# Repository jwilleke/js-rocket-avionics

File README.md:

# js-rocket-avionics

Carrier PCB and flight firmware for the [js-rocket](https://github.com/jwilleke/js-rocket) electronics sled.

__This is one candidate payload for the rocket, not *the* payload.__ The rocket flies on ballast alone. The interface it has to satisfy — 40.0 mm bore × 150 mm, an M3 × 55 retainer at nose z 15, a ~50 g mass ceiling, an optional camera port — is [`js-rocket/docs/payload-bay.md`](https://github.com/jwilleke/js-rocket/blob/main/docs/payload-bay.md), and that is the only page in that repo this project depends on.

__Flying the rocket, not building it? Read [docs/using-avionics.md](docs/using-avionics.md)__ — what the electronics do, and what to do before, during and after a flight. Everything below is for builders.

Separate from the rocket repo on purpose: `js-rocket` is geometry and documentation with no code, no package manager and no dependencies, and its `CLAUDE.md` says so explicitly. Copper, firmware and __the design record — every decision and why, in [docs/design.md](docs/design.md)__ — live here instead.

__Why it is built this way is in [docs/design.md](docs/design.md).__ __Every part this project needs is in [docs/BOM.md](docs/BOM.md), which is the single source of truth for part numbers and weights__ — plus what each part is, which board it serves, and what was rejected. __What to change next time, and what can be bought ready-made, is in [docs/next-electronics.md](docs/next-electronics.md).__ __What was actually bought is in [docs/shopping-list.md](docs/shopping-list.md)__ — orders, costs, arrival status. The printed sled that carries these boards, and the [PayloadAdapter](https://github.com/jwilleke/js-rocket/blob/main/docs/3d-printed-parts/payload-adapter.md) it loads through, are rocket parts and stay in [js-rocket](https://github.com/jwilleke/js-rocket).

__Status: one two-sided board ([PCB-carrier-design.md](hardware/PCB-carrier/PCB-carrier-design.md)), placed, netted and routed. DRC: 0 violations, 0 unconnected.__ The generator routes the signal nets itself ([`carrier_router.py`](hardware/scripts/carrier_router.py), [#15](https://github.com/jwilleke/js-rocket-avionics/issues/15)); ground and 3.3 V reach every pad through the two inner planes. What the board is, both sides with a drawing, is [hardware/PCB-carrier/PCB-carrier.md](hardware/PCB-carrier/PCB-carrier.md).

> __Do not order it yet.__ Left before ordering: the reprinted fit mock, fitted, and the pre-order review — regenerate the fabrication files from this board and read its connections back ([#16](https://github.com/jwilleke/js-rocket-avionics/issues/16)).

## What a flight records

__Planned, not yet written.__ The recorder firmware on XIAO-ESP32S3-cam is __not started__ — today a flight would record nothing. The GPS is not recorded at all; its only copy is what the ground receiver hears.

| Data | From | Recorded? | Where it ends up |
|---|---|---|---|
| Acceleration and rotation | [LSM6DSO32](hardware/LSM6DSO32/LSM6DSO32.md), XIAO-ESP32S3-cam | __planned__ — 500 Hz, read from the sensor's FIFO | PSRAM through the flight (~900 KB a minute), __written to microSD in slices as it goes__ |
| Pressure, so altitude | [BMP388](hardware/BMP388-barometer/BMP388-barometer.md), XIAO-ESP32S3-cam | __planned__ — in the same log | the same |
| Video | OV3660 on the [Sense camera board](hardware/Sense-camera-board/Sense-camera-board.md), XIAO-ESP32S3-cam | __planned__ — from launch, with a few seconds before it, until landing is detected; idle on the pad | microSD, as it records |
| Position and GPS altitude | [L76K-GNSS](hardware/L76K-GNSS/L76K-GNSS.md), XIAO-ESP32S3-lora | __no__ — broadcast over LoRa by stock Meshtastic every so often, stored nowhere on the rocket | the ground receiver and the phone on it — [#23](https://github.com/jwilleke/js-rocket-avionics/issues/23), ordered 2026-09-11 |

__Two things that follow:__

- __A reset of XIAO-ESP32S3-cam in flight loses the slice of the sensor log not yet on the card__ — the rest is already written. Whether the shared battery browns it out is [#8](https://github.com/jwilleke/js-rocket-avionics/issues/8)
- __The sensor log has no GPS in it.__ The two XIAOs share power and nothing else, so position and motion are never in one record

Why the log sits in PSRAM rather than going straight to the card: [design.md](docs/design.md#data-path--why-the-log-lives-in-psram).

## The interface to the sled

__One board on the PayloadSled's centre line__, hanging off the web on two standoffs: the tall side (both XIAO stacks) faces 270°, the camera port; the low side (sensors, standoffs) faces 90°, the web. The sled side is [js-rocket#99](https://github.com/jwilleke/js-rocket/issues/99), which moves the web toward 90° and drills it at the standoffs. __Change these and the sled changes.__

| | Value |
|---|---|
| Board | __24.0 × 115.7 mm__, aft end at nose z 25.4, forward end 141.1 |
| Thickness | __1.6 mm__, 4 copper layers — OSH Park's only 4-layer thickness |
| Corner radius | 2.0 mm |
| Standoffs | __2 plain M3 holes__ (3.2 mm) at board (x, y) __(12.0, 4.0)__ and __(16.5, 110.5)__ — nose z 29.4 and 135.9, neither under a module. A __female-female M3 hex standoff__, 10 mm, between the board's low face and the web, a screw into it from each side, as on the fit mock — nothing soldered |
| XIAO-ESP32S3-cam centre | board y __18.0__ (nose z 43.4), under the camera pad |
| XIAO-ESP32S3-lora centre | board y __41.4__ (nose z 66.8), turned 90° |

Board x runs across the board, y from the aft end, forward positive, in KiCad's top view (the tall side). Everything above is read out of the generated board by `gen_carrier.py`; the gerbers in `fab/` predate it ([#16](https://github.com/jwilleke/js-rocket-avionics/issues/16)).

__Why 24 mm wide.__ It matches the web. The sensors fit across it or hang just past its edges, below the web — [PCB-carrier.md](hardware/PCB-carrier/PCB-carrier.md#low-side--faces-90-the-web).

__Why 115.7 mm long.__ The camera fixes the cam XIAO at the aft end, and the tall side then carries the lora XIAO, the L76K-GNSS, the data-link jumpers and the buzzer end to end. The low side carries the battery as well as the sensors (layout B2, 2026-09-15): LSM6DSO32 aft, the battery behind the lora XIAO and the L76K, the BMP388 forward of it, turned across the board under the buzzer ([#36](https://github.com/jwilleke/js-rocket-avionics/issues/36)). 90.4 mm until the battery moved onto the board.

__Why 1.6 mm.__ It is the only thickness OSH Park makes a 4-layer board in — "63mil (1.6mm) nominal". The 1.0 mm this page carried until 2026-09-15 was never checked against the fab; the operator caught it on the printed fit mock ("looks too thin"). It is also the better board: the standoffs are now __106.5 mm apart__ (81 before 2026-09-15), and 1.6 mm is __about 4× as stiff__ as 1.0 over that span (stiffness goes as thickness cubed). The low face — the standoffs' face — stays at r 0.5, so the sled does not change; the tall side moves __0.6 mm toward 270°__. What that costs across the bore is in [PCB-carrier-design.md](hardware/PCB-carrier/PCB-carrier-design.md#across-the-bore)

## The XIAO stack

__The expansion board — Sense or Wio-SX1262 — sits above the XIAO__, on the B2B connector on its front face. The XIAO stands on __two standard 7-pin headers__, ~2.50 mm, onto the board. No cutout and no tall stacking headers are needed. Stack heights and the fit across the bore are in [docs/design.md](docs/design.md#headers-and-the-expansion-board-on-top).

## Connections

There is __no schematic file__. Nets are assigned to pads directly in the generator, which is more robust than hand-authoring schematic s-expressions for 11 nets and keeps one generator as the single source of truth. The cost is no ERC and no drawn diagram — so this table *is* the wiring diagram. __Keep it in step with `gen_carrier.py`.__

| Net | From | Also reaches |
|---|---|---|
| `GND` | both XIAOs, pin 13 | In1 plane, every module |
| `+3V3` | XIAO-ESP32S3-cam pin 12 __only__ | In2 plane; LSM6DSO32 `VIN`; BMP388 `VIN` __and `CS`__ (I2C mode, [#19](https://github.com/jwilleke/js-rocket-avionics/issues/19)) |
| `+3V3_LORA` | XIAO-ESP32S3-lora pin 12 | the L76K-GNSS's `3V3` only — __kept off the plane__, so the two regulators are never paralleled |
| `SDA` | cam __D4__ (pin 5, GPIO5) | LSM6DSO32, BMP388 |
| `SCL` | cam __D5__ (pin 6, GPIO6) | LSM6DSO32, BMP388 |
| `BUZZER` | cam __D0__ (pin 1, GPIO1) | one buzzer lead (`TP_BUZ`); the PS1240 sits on the tall side's forward end |
| `BUZZER_B` | cam __D2__ (GPIO3) | the other buzzer lead (`TP_BUZ_G`), driven in opposite phase to `BUZZER` for about +6 dB ([#25](https://github.com/jwilleke/js-rocket-avionics/issues/25)) |
| `GPS_TX` | lora __D6__ (pin 7, GPIO43) | the L76K-GNSS's pad at the D6 position, which is the module's __RX__ |
| `GPS_RX` | lora __D7__ (pin 8, GPIO44) | the L76K-GNSS's pad at the D7 position, which is the module's __TX__ |
| `LINK_GPS` | the GPS link's 2-pin header, pin 2 (pin 1 is on `GPS_RX`) | its 1 kΩ, whose far end is `GPS_CAM` |
| `LINK_EVT` | the event link's 2-pin header, pin 1 | its 1 kΩ, whose far end is `EVT_CAM` |
| `GPS_CAM` | XIAO-ESP32S3-cam __D1__ (GPIO2) | the GPS link's 1 kΩ: the cam XIAO hears the GPS ([#26](https://github.com/jwilleke/js-rocket-avionics/issues/26)) |
| `EVT_CAM` | XIAO-ESP32S3-cam __D3__ (GPIO4) | the event link's 1 kΩ: event text out |
| `EVT_LORA` | XIAO-ESP32S3-lora __D1__ (GPIO2) | the event link's 2-pin header, pin 2: Meshtastic's Serial module receives here. Stock Meshtastic leaves D1 free ([#26](https://github.com/jwilleke/js-rocket-avionics/issues/26)) |

`GPS_TX` and `GPS_RX` are named from the XIAO's side. __Wire the L76K-GNSS by position, never by its silkscreen word__ — [L76K-GNSS.md](hardware/L76K-GNSS/L76K-GNSS.md#pinout--from-seeeds-schematic-not-the-listing).

### The pin map, and an error worth not repeating

The KiCad footprint numbers its pads 1–14 with no signal names, DIP-style — 1 at top-left, down to 7 at bottom-left, 8 at bottom-right, up to 14 at top-right. Seeed's pinout gives the meaning:

```text
pin  1  2  3  4  5  6  7   8  9  10  11   12   13   14
sig  D0 D1 D2 D3 D4 D5 D6  D7 D8 D9  D10  3V3  GND  5V
```

An earlier revision of the generator put GPS on pins 6/7 and I2C on 4/5 — which are __D5/D6 and D3/D4, every one off by one__. Caught by reading the mapping back out of the saved board rather than trusting the script's own output. The generator now names pins (`XIAO_PIN["D6"]`) so the numbers never appear by hand.

__Each 1×7 header numbers its own pads 1–7.__ The second row's pad 1 is XIAO pin 8, at the far end, so `xiao_pin = pad + 7` running back toward the USB-C. This file once said `15 − pad`, which is [#18](https://github.com/jwilleke/js-rocket-avionics/issues/18)'s mirrored row, written down as the rule.

## The GPS is an L76K

The MAX-M10S was rejected on 2026-08-06: __44.2 × 30.5 mm — wider than this 24 mm board — and ~$60__. The chosen part is Seeed's __L76K GNSS for XIAO (109100021)__ — 18 × 21 mm, UART on __D6/D7__. It takes its own footprint on the tall side, forward of the lora XIAO ([where](hardware/PCB-carrier/PCB-carrier.md#tall-side--faces-270-the-camera)), and its antenna is a separate part on the sled. Pinout, power and orientation: [L76K-GNSS.md](hardware/L76K-GNSS/L76K-GNSS.md).

The same staleness once reached the barometer: __BMP390 → BMP388__, settled on 2026-08-06 when the 390 went out of stock. Same BMP3xx driver, same 25.5 × 17.8 mm STEMMA QT outline, address 0x77, and its pinout __confirmed off the physical part__.

## Battery — read before assembling

__BAT+/BAT− are underside pads on the XIAO__, not brought out to the castellated edge, so the battery cannot reach a XIAO through the headers. The battery reaches each XIAO through a __Y-cable__, off the board, and a short __soldered pigtail__ on its BAT pads.

- __Solder the pigtails before the XIAO goes onto its headers.__ The board, not the expansion board, is what covers the pads.
- __On battery power there is no voltage on the 5V pin__ — nothing can be fed from a XIAO's 5V rail.
- Both XIAO chargers sit in parallel on one battery. __Charge through one USB port at a time__, and read [why that is not sufficient on its own](hardware/LiPo-500mAh/LiPo-500mAh.md#two-chargers-on-one-battery).
- __The battery is not on the board.__ A Y-cable joins it to both XIAOs' pigtails ([LiPo-500mAh.md](hardware/LiPo-500mAh/LiPo-500mAh.md#the-y-cable)). Check every new cable's polarity with a meter; reversing a LiPo into a XIAO destroys it.

## No RF on this board

The L76K and the Wio-SX1262 each carry their own U.FL connector, and both antennas mount on the sled, so __no RF ever crosses the carrier__. It is a purely digital and power board of 9 nets, which is what makes it tractable to generate and verify headlessly.

## Building

Requires KiCad 10. The generator uses KiCad's bundled Python so `pcbnew` matches the CLI exactly.

```bash
KPY=/Applications/KiCad/KiCad.app/Contents/Frameworks/Python.framework/Versions/3.9/bin/python3
CLI=/Applications/KiCad/KiCad.app/Contents/MacOS/kicad-cli

$KPY hardware/scripts/gen_carrier.py
$CLI pcb drc  --format json -o /tmp/drc.json hardware/PCB-carrier/PCB-carrier.kicad_pcb
$CLI pcb export gerbers -o fab/gerbers/ hardware/PCB-carrier/PCB-carrier.kicad_pcb
$CLI pcb export drill   -o fab/gerbers/ hardware/PCB-carrier/PCB-carrier.kicad_pcb
```

__The board is generated, not hand-edited.__ `.kicad_pcb` format shifts between KiCad releases; building it through `pcbnew` means the file is written by the same code that reads it. Edit `hardware/scripts/gen_carrier.py` and re-run — do not edit the board file directly, or the next run overwrites you.

`gen_outline.py` is the superseded 2a-only version, kept for reference.

DRC must report __0 violations__ before anything is ordered.

## Remaining stages

| Stage | State |
|---|---|
| 2a — outline, standoffs, stackup | __done__, one two-sided board |
| 2b — nets + footprints | __done__ — every footprint placed and netted |
| 2b — GND/+3V3 planes | __done__, In1 and In2 filled |
| 2c — placement | __done in the generator__, pending review of the drawing — [#14](https://github.com/jwilleke/js-rocket-avionics/issues/14) |
| 2d — signal routing | not started — [#15](https://github.com/jwilleke/js-rocket-avionics/issues/15) |
| 2e — Gerber + drill for fab | chain proven; needs a finished board |

__Do not order copper before breadboarding.__ A layout error costs ~$43 and two weeks; a wiring error costs minutes.

Fab target is __OSH Park__. The 24 × 70 mm version quoted **$26.00 for 3 copies** — OSH Park's 4-layer price is $10/in² for three — so 24 × 115.7 mm (4.30 in²) should land near __$43__. Re-upload to confirm; three copies — one to fly, two spares.

__OSH Park accepts the `.kicad_pcb` directly__ — confirmed by upload, not assumed. It read the layer count and outline unaided, so `fab/gerbers/` is not in the ordering path and exists only as a check that the export chain works.

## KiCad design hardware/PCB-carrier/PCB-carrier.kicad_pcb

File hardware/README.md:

# Hardware

__One page per part, and the source of truth for the hardware in use.__ What each part is, its interfaces and dimensions, and the traps that are properties of the object.

__These pages are not a history and not a task list.__ They say what is, not what changed or what to do next. Decisions and open work live in [issues](https://github.com/jwilleke/js-rocket-avionics/issues); what happened in a session lives in `private/project_log.md`; the reasoning behind the design lives in [design.md](../docs/design.md).

__These pages also fix the vocabulary.__ A part is called by the name of its page here — [XIAO-ESP32S3-cam](XIAO-ESP32S3-cam/XIAO-ESP32S3-cam.md) and [XIAO-ESP32S3-lora](XIAO-ESP32S3-lora/XIAO-ESP32S3-lora.md), never "board A" and "board B" — and where a page has a plain-English word for the thing, that word is the one to use. __The [LiPo-500mAh](LiPo-500mAh/LiPo-500mAh.md) is the battery.__ It is not "the cell": that is a word from datasheets, it reads as jargon to everyone who has to work on this, and one battery made of one cell gains nothing by the distinction.

## The names, and where they live

__One folder per part. The folder, the page inside it and the part all carry the same name.__ Adopted 2026-09-09. `hardware/BMP388-barometer/BMP388-barometer.md` — not `README.md`, because a folder that already names the part does not need a second word for it. __A part's own photographs live in its folder__, beside its page.

__These are the names. Nothing else is a name for these things:__

| Folder and page | Is |
|---|---|
| `XIAO-ESP32S3-cam` | The MCU module carrying the camera. Never "board B", never "the Sense one" |
| `XIAO-ESP32S3-lora` | The MCU module carrying the radio. Never "board A" |
| `Sense-camera-board` | The expansion board on XIAO-ESP32S3-cam |
| `Wio-SX1262-LoRa` | The LoRa radio |
| `L76K-GNSS` | The GNSS module |
| `LSM6DSO32` | The IMU |
| `BMP388-barometer` | The barometer |
| `PS1240-buzzer` | The buzzer |
| `LiPo-500mAh` | __The battery.__ Never "the cell" |
| `Arming-switch` | The arming switch. __Not the JST__, which is a connector |
| `Stacking-headers` | The 7-pin strips |
| `Antennas` | Both U.FL antennas |
| `microSD` | The card |
| `PCB-carrier` | The carrier board |
| `LiPo-charger` | The battery's own USB charger, off the rocket. Not "the charger" alone — each XIAO has one built in too |
| `camera-stack` | XIAO-ESP32S3-cam __with__ its Sense board — the assembly, not either part |
| `GNSS-stack` | __A rejected arrangement, not a thing that exists.__ Kept so it is not proposed again |

__Where a part has no folder here, it is not a part of this payload.__ "XIAO" on its own is not a name: there are two of them and they are not interchangeable.

__Two exceptions to "photographs live with the part".__ [`docs/resources/`](../docs/resources/) keeps the images that belong to __both__ XIAO modules — the front and back pinouts, the module and underside shots — because they document the model rather than either role, and a second copy is a copy that drifts. [`docs/bench-work/`](../docs/bench-work/) keeps what belongs to no part at all: the breadboard drawing, the bench photograph and the measurement grid.

__These pages hold no part numbers and no masses.__ [BOM.md](../docs/BOM.md) owns both and says so: *"anything else that quotes a part number or a mass is wrong — link here instead."* A number in two places is a number that will disagree with itself.

| | Page | Goes with | Photos | What it is |
|---|---|---|---|---|
| MCU | [XIAO-ESP32S3-lora.md](XIAO-ESP32S3-lora/XIAO-ESP32S3-lora.md) | — | grid | The MCU module. __Runs stock Meshtastic__ — identical to the cam copy to look at; [which is which](XIAO-ESP32S3-lora/XIAO-ESP32S3-lora.md#which-xiao-is-this-one) |
| MCU | [XIAO-ESP32S3-cam.md](XIAO-ESP32S3-cam/XIAO-ESP32S3-cam.md) | — | grid + bench | The MCU module. On the bench with both sensors and the buzzer; runs `bringup-cam` |
| Payload | [Sense-camera-board.md](Sense-camera-board/Sense-camera-board.md) | XIAO-ESP32S3-cam | grid ×2 | OV3660 camera and the microSD slot |
| Radio | [Wio-SX1262-LoRa.md](Wio-SX1262-LoRa/Wio-SX1262-LoRa.md) | XIAO-ESP32S3-lora | grid | LoRa. Buy as the matched kit, never separately |
| GNSS | [L76K-GNSS.md](L76K-GNSS/L76K-GNSS.md) | XIAO-ESP32S3-lora | grid | Position. __Flat on the carrier's tall side__, own footprint |
| Sensor | [LSM6DSO32.md](LSM6DSO32/LSM6DSO32.md) | carrier | grid + back | ±32 g IMU with a 9 KB FIFO |
| Sensor | [BMP388-barometer.md](BMP388-barometer/BMP388-barometer.md) | carrier | grid + 2 close | Unported barometer, 0x77 |
| Output | [PS1240-buzzer.md](PS1240-buzzer/PS1240-buzzer.md) | carrier | __none__ | Passive piezo. The only status channel on the pad |
| Power | [LiPo-500mAh.md](LiPo-500mAh/LiPo-500mAh.md) | carrier | __none__ | One battery, both XIAOs |
| Power | [LiPo-charger.md](LiPo-charger/LiPo-charger.md) | off the rocket | __none__ | Charges the battery at its own plug, below the sled |
| Power | [Arming-switch.md](Arming-switch/Arming-switch.md) | battery lead | __n/a__ | In the battery line. __Flight 3 carries none__ |
| Storage | [microSD.md](microSD/microSD.md) | Sense camera board | __none__ | Video only |
| RF | [Antennas.md](Antennas/Antennas.md) | Wio-SX1262, L76K | grid | Both off-board on U.FL. ≥50 mm apart |
| Mechanical | [Stacking-headers.md](Stacking-headers/Stacking-headers.md) | both XIAOs | __none__ | 7-pin strips, ~2.50 mm standoff |
| Mechanical | [PCB-carrier.md](PCB-carrier/PCB-carrier.md) | everything | __n/a__ | The board, and the sled's structural span |
| Assembly | [camera-stack.md](camera-stack/camera-stack.md) | — | end + side | XIAO-ESP32S3-cam with its Sense board, as one object |
| Assembly | [GNSS-stack.md](GNSS-stack/GNSS-stack.md) | — | __none__ | __Rejected.__ Why the L76K is not in a stack |

## Photographs

__Each part's images live in that part's folder__, beside its page; the two shared XIAO images stay in [`docs/resources/`](../docs/resources/). Every one is embedded on the page above. __Shot on the printed measurement grid__ — part flat, square-on, calibration bar in frame. Method and its precision: [module-pinouts.md](../docs/module-pinouts.md#how-these-are-measured--photograph-on-the-grid-not-calipers).

| Image | Part | What it is for |
|---|---|---|
| [`BMP388-front-grid.jpg`](BMP388-barometer/BMP388-front-grid.jpg) | BMP388 | __Dimensional record.__ Header row along the bottom, mounting holes at the top corners |
| [`BMP388-front.jpg`](BMP388-barometer/BMP388-front.jpg) | BMP388 | Close-up. Confirms pin order on the silkscreen |
| [`BMP388-back.jpg`](BMP388-barometer/BMP388-back.jpg) | BMP388 | Close-up. Address jumper, `3 V` marking |
| [`LSM6DSO32-front.jpg`](LSM6DSO32/LSM6DSO32-front.jpg) | LSM6DSO32 | __Dimensional record.__ Both header rows and both mounting holes |
| [`LSM6DSO32-back.jpg`](LSM6DSO32/LSM6DSO32-back.jpg) | LSM6DSO32 | Close-up. `ST LSM6DSO32`, ±32 g, `0x6A` |
| [`L76K-GNSS.jpg`](L76K-GNSS/L76K-GNSS.jpg) | L76K | Module and its ≈25 mm patch antenna, to scale |
| [`Wio-SX1262-LoRa.jpg`](Wio-SX1262-LoRa/Wio-SX1262-LoRa.jpg) | Wio-SX1262 | FCC ID, U.FL, and the 2×5 header currently fitted |
| [`Wio-SX1262-LoRa-antennas.jpg`](Wio-SX1262-LoRa/Wio-SX1262-LoRa-antennas.jpg) | Antennas | Both Seeed strips, to scale |
| [`XIAO-ESP32S3-module.jpg`](../docs/resources/XIAO-ESP32S3-module.jpg) | XIAO ×2 | The MCU board. USB-C, U.FL, B2B, 14 pads |
| [`XIAO-ESP32-S3-bottom.jpg`](../docs/resources/XIAO-ESP32-S3-bottom.jpg) | XIAO ×2 | __The pin labels.__ Underside, where the silkscreen is — the only reading that confirms pad 1 is `D0`. See [module-pinouts.md](../docs/module-pinouts.md#xiao-esp32s3--read-off-the-underside-2026-09-08) |
| [`2026-09-12-XIAO-ESP32S3-cam-bench.jpg`](XIAO-ESP32S3-cam/2026-09-12-XIAO-ESP32S3-cam-bench.jpg) | XIAO-ESP32S3-cam | __Bench, not grid.__ The cam breadboard, sensors and buzzer wired, no Sense board — with the I2C wires on D3/D4, the slip since fixed |
| [`XIAO-ESP32S3-Sense-expansion.jpg`](Sense-camera-board/XIAO-ESP32S3-Sense-expansion.jpg) | Sense | Camera and microSD board |
| [`XIAO-ESP32S3-Sense-stack-end.jpg`](camera-stack/XIAO-ESP32S3-Sense-stack-end.jpg) | camera-stack | __End-on.__ Settled that the expansion board mates to the front face and sits above |
| [`XIAO-ESP32S3-Sense-stack-side.jpg`](camera-stack/XIAO-ESP32S3-Sense-stack-side.jpg) | camera-stack | The same assembly from the side |

## The two stacks

__Name everything by its page.__ There is no "board A", no "board B", and no functional nickname — the two MCU modules are told apart by which expansion board is on them, which is what their filenames say.

| | Mated to it | Firmware |
|---|---|---|
| __XIAO-ESP32S3-lora__ | [Wio-SX1262](Wio-SX1262-LoRa/Wio-SX1262-LoRa.md) radio, [L76K](L76K-GNSS/L76K-GNSS.md) GNSS | __none written__ — stock Meshtastic, pre-flashed |
| __XIAO-ESP32S3-cam__ | [Sense camera board](Sense-camera-board/Sense-camera-board.md) | custom, not started |

__The two XIAO modules are the same part but not interchangeable in practice__ — the lora one arrived with its 7-pin headers soldered on, the cam one did not.

Both ride the one [carrier PCB](PCB-carrier/PCB-carrier.md), on its tall side. The IMU and barometer sit on its low side, not on either expansion board. The buzzer is on the tall side's forward end; both antennas are off the board.

## Fasteners

__The carrier hangs off the sled's web on two female-female M3 hex standoffs__, 10 mm, through two plain M3 holes, with a screw into each standoff from each side: one through the board from its tall side, one through the web from its far face (operator, 2026-10-17, as fitted on the mock; [PCB-carrier.md](PCB-carrier/PCB-carrier.md)). Nothing is soldered. The old "M2 everywhere" standard (2026-09-05) was for screwing the breakouts down, which is no longer done.

__The sensors are not screwed through the board__, because nothing may stick out of its back: the LSM6DSO32 is soldered by both its rows, and the BMP388's free edge rests on __two spacers in its own holes__, standing on the board's low face — no bolt ([BMP388-barometer.md](BMP388-barometer/BMP388-barometer.md#mounting)). Nothing on the avionics takes an M2.

__Printed holes are modelled oversize.__ A hole modelled at nominal prints undersize by ~0.3 mm on the P2S, so the sled's M3 holes are drawn for clearance rather than at 3.0 — the same rule as the anchor bore in the rocket repo.

## What is not here

- __KiCad sources__ — [`PCB-carrier/`](PCB-carrier/), beside the page that documents the board
- __Generators__ — `scripts/`, including `gen_carrier.py`
- __Measured pin order and caliper readings__ — [module-pinouts.md](../docs/module-pinouts.md)
- __Why it is built this way__ — [design.md](../docs/design.md)
- __Bench drawings and the measurement grid__ — [`docs/bench-work/`](../docs/bench-work/)

---

Part numbers, vendors and masses live in [BOM.md](../docs/BOM.md), which is the single source of truth for both. Purchase history is in [shopping-list.md](../docs/shopping-list.md); the reasoning is in [design.md](../docs/design.md).

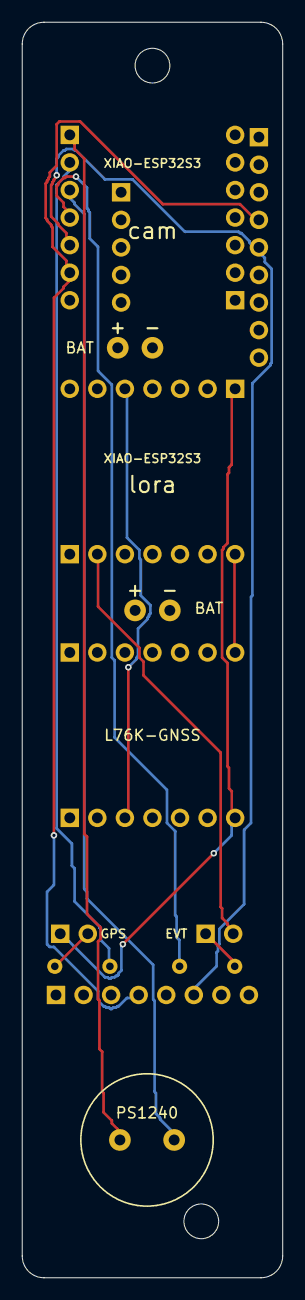
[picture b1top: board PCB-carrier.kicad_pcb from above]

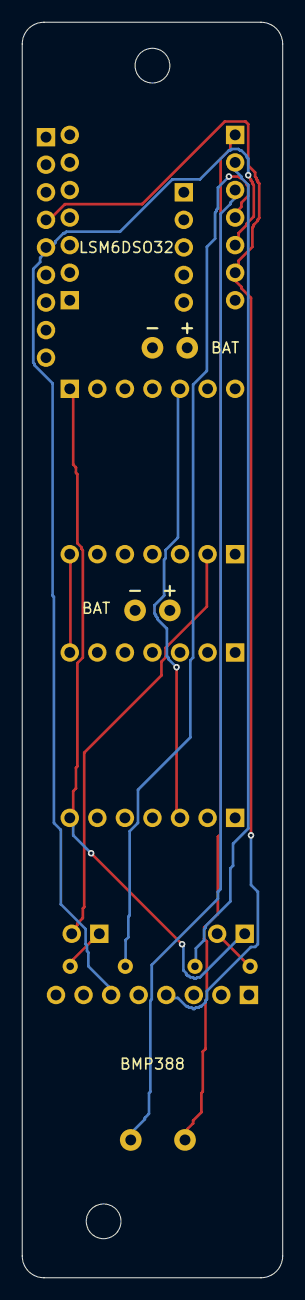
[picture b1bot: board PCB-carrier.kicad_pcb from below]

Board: 4 copper layers, 24.0 x 115.7 mm, 21 parts (3 on the bottom side), 14 nets.

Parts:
J_BMP: PinHeader_1x08_P2.54mm_Vertical
J_CAM_A: PinHeader_1x07_P2.54mm_Vertical
J_CAM_B: PinHeader_1x07_P2.54mm_Vertical
J_L76K_A, J_L76K_B: PinHeader_1x07_P2.54mm_Vertical
J_LINK_EVT: PinHeader_1x02_P2.54mm_Vertical
J_LINK_GPS: PinHeader_1x02_P2.54mm_Vertical
J_LORA_A: PinHeader_1x07_P2.54mm_Vertical
J_LORA_B: PinHeader_1x07_P2.54mm_Vertical
J_LSM_A: PinHeader_1x05_P2.54mm_Vertical
J_LSM_P: PinHeader_1x09_P2.54mm_Vertical
R_LINK_EVT: R_Axial_DIN0204_L3.6mm_D1.6mm_P5.08mm_Horizontal
R_LINK_GPS: R_Axial_DIN0204_L3.6mm_D1.6mm_P5.08mm_Horizontal
SO1, SO2: MountingHole_3.2mm_M3
TP_BUZ: TestPoint_THTPad_D2.0mm_Drill1.0mm
TP_BUZ_G: TestPoint_THTPad_D2.0mm_Drill1.0mm
TP_CAM_BAT_N: TestPoint_THTPad_D2.0mm_Drill1.0mm
TP_CAM_BAT_P: TestPoint_THTPad_D2.0mm_Drill1.0mm
TP_LORA_BAT_N: TestPoint_THTPad_D2.0mm_Drill1.0mm
TP_LORA_BAT_P: TestPoint_THTPad_D2.0mm_Drill1.0mm

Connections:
+3V3: J_BMP.1, J_BMP.7, J_CAM_B.5, J_LSM_P.1
+3V3_LORA: J_L76K_A.3, J_LORA_B.5
BUZZER: J_CAM_A.1, TP_BUZ.1
BUZZER_B: J_CAM_A.3, TP_BUZ_G.1
EVT_CAM: J_CAM_A.4, R_LINK_EVT.1
EVT_LORA: J_LINK_EVT.2, J_LORA_A.2
GND: J_BMP.3, J_CAM_B.6, J_L76K_A.2, J_LORA_B.6, J_LSM_P.3
GPS_CAM: J_CAM_A.2, R_LINK_GPS.2
GPS_RX: J_L76K_A.7, J_LINK_GPS.1, J_LORA_B.1
GPS_TX: J_L76K_B.7, J_LORA_A.7
LINK_EVT: J_LINK_EVT.1, R_LINK_EVT.2
LINK_GPS: J_LINK_GPS.2, R_LINK_GPS.1
SCL: J_BMP.4, J_CAM_A.6, J_LSM_P.4
SDA: J_BMP.6, J_CAM_A.5, J_LSM_P.5

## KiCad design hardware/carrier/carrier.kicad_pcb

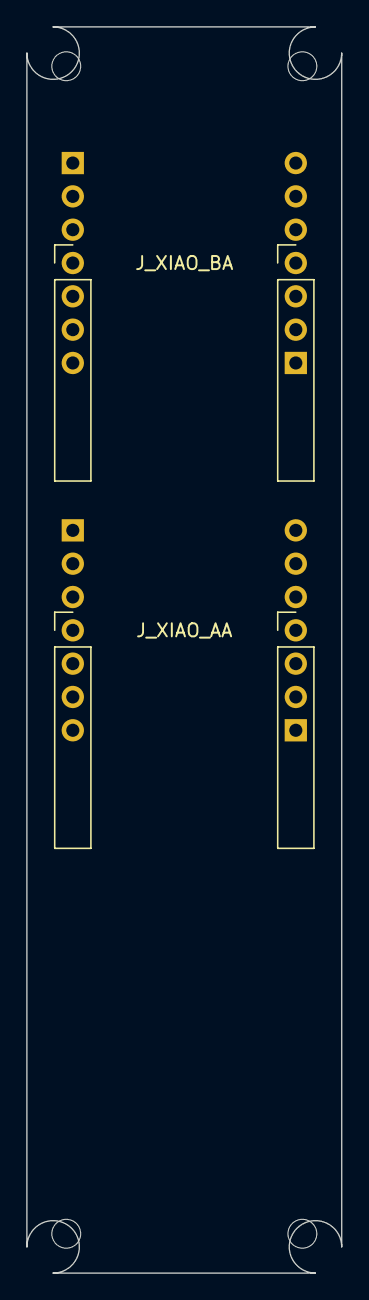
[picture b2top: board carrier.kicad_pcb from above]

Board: 4 copper layers, 24.0 x 95.0 mm, 8 parts (0 on the bottom side), 2 nets, no tracks yet.

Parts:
H1, H2, H3, H4: MountingHole_2.2mm_M2
J_XIAO_AA: PinHeader_1x07_P2.54mm_Vertical
J_XIAO_AB: PinHeader_1x07_P2.54mm_Vertical
J_XIAO_BA: PinHeader_1x07_P2.54mm_Vertical
J_XIAO_BB: PinHeader_1x07_P2.54mm_Vertical

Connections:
+3V3: J_XIAO_AB.3, J_XIAO_BB.3
GND: J_XIAO_AB.2, J_XIAO_BB.2
